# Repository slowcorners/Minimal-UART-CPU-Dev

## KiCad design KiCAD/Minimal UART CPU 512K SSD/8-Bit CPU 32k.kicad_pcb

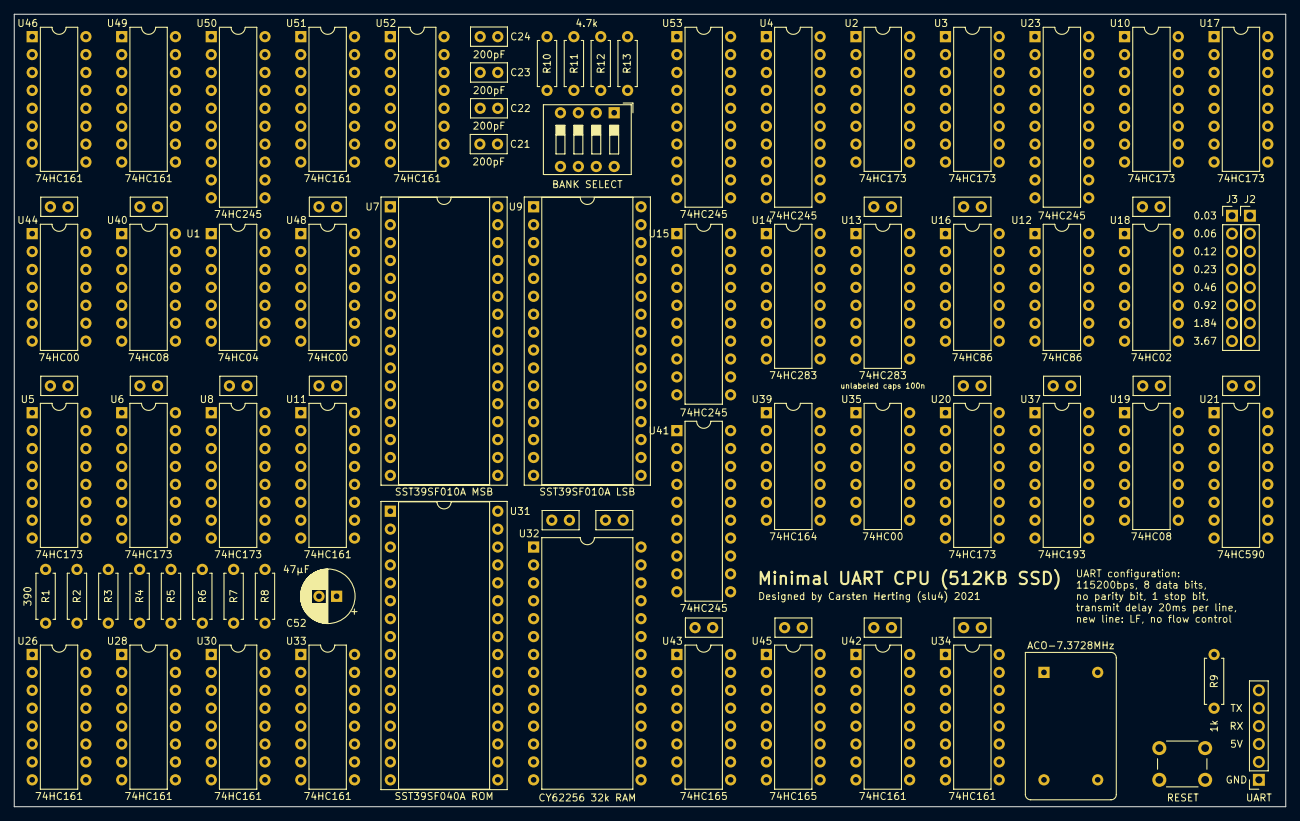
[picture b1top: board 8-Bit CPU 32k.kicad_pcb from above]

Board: 2 copper layers, 180.3 x 112.4 mm, 89 parts (0 on the bottom side), 170 nets, no tracks yet.

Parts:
C1, C2, C3, C4, C5, C6, C7, C8, C9, C10, C11, C12, C13, C14, C15, C16, C17, C18, C19, C20: 100nF; C_Disc_D5.0mm_W2.5mm_P2.50mm
C21, C22, C23, C24: 200pF; C_Disc_D5.0mm_W2.5mm_P2.50mm
C52: 47µF; CP_Radial_D7.5mm_P2.50mm
J1: UART; PinSocket_1x06_P2.54mm_Vertical
J2: CLOCK; PinHeader_1x08_P2.54mm_Vertical
J3: SELECT; PinHeader_1x08_P2.54mm_Vertical
R1, R2, R3, R4, R5, R6, R7, R8: 390; R_Axial_DIN0207_L6.3mm_D2.5mm_P7.62mm_Horizontal
R9: 1k; R_Axial_DIN0207_L6.3mm_D2.5mm_P7.62mm_Horizontal
R10, R11, R12, R13: 4.7k; R_Axial_DIN0207_L6.3mm_D2.5mm_P7.62mm_Horizontal
SW1: RESET; SW_PUSH_6mm
SW2: BANK SELECT; SW_DIP_SPSTx04_Slide_9.78x12.34mm_W7.62mm_P2.54mm
U1: 74HC04; DIP-14_W7.62mm
U2, U3, U5, U6, U8, U10, U17, U20: 74HC173; DIP-16_W7.62mm
U4, U15, U23, U41, U50, U53: 74HC245; DIP-20_W7.62mm
U7: SST39SF010A MSB; DIP-32_W15.24mm_Socket
U9: SST39SF010A LSB; DIP-32_W15.24mm_Socket
U11, U26, U28, U30, U33, U34, U42, U46, U49, U51, U52: 74HC161; DIP-16_W7.62mm
U12, U16: 74HC86; DIP-14_W7.62mm
U13, U14: 74HC283; DIP-16_W7.62mm
U18: 74HC02; DIP-14_W7.62mm
U19, U40: 74HC08; DIP-14_W7.62mm
U21: 74HC590; DIP-16_W7.62mm
U31: SST39SF040A ROM; DIP-32_W15.24mm_Socket
U32: CY62256 32k RAM; DIP-28_W15.24mm
U35, U44, U48: 74HC00; DIP-14_W7.62mm
U37: 74HC193; DIP-16_W7.62mm
U39: 74HC164; DIP-14_W7.62mm
U43, U45: 74HC165; DIP-16_W7.62mm
X1: ACO-7.3728MHz; Oscillator_DIP-14

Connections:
1.8432MHz: J3.2, U21.1, U34.2, U42.2
+5V: C1.1, C2.1, C3.1, C4.1, C5.1, C6.1, C7.1, C8.1, C9.1, C10.1, C11.1, C12.1, C13.1, C14.1, C15.1, C16.1, C17.1, C18.1, C19.1, C20.1, C52.1, J1.3, R1.1, R2.2, R3.2, R4.2, R5.2, R6.2, R7.2, R8.2, R9.2, SW2.5, SW2.6, SW2.7, SW2.8, U1.14, U2.16, U3.16, U4.1, U4.20, U5.16, U6.16, U7.31, U7.32, U8.16, U9.31, U9.32, U10.16, U11.7, U11.9, U11.10, U11.16, U12.14, U13.16, U14.16, U15.20, U16.14, U17.16, U18.14, U19.14, U20.16, U21.10, U21.16, U23.1, U23.20, U26.1, U26.16, U28.1, U28.16, U30.1, U30.16, U31.32, U32.28, U33.1, U33.16, U34.7, U34.9, U34.10, U34.16, U35.14, U37.5, U37.9, U37.15, U37.16, U39.2, U39.9, U39.14, U40.14, U41.1, U41.20, U42.7, U42.9, U42.10, U42.16, U43.6, U43.16, U44.14, U45.3, U45.4, U45.10, U45.11, U45.12, U45.13, U45.14, U45.16, U46.16, U48.14, U49.16, U50.20, U51.16, U52.16, U53.20, X1.14
/ALU/A0: U3.3, U4.2, U14.5
/ALU/A1: U3.4, U4.3, U14.3
/ALU/A2: U3.5, U4.4, U14.14
/ALU/A3: U3.6, U4.5, U14.12
/ALU/A4: U2.3, U4.6, U13.5
/ALU/A5: U2.4, U4.7, U13.3
/ALU/A6: U2.5, U4.8, U13.14
/ALU/A7: U2.6, U4.9, U13.12
/ALU/B0: U16.13, U17.3, U23.2
/ALU/B1: U16.10, U17.4, U23.3
/ALU/B2: U16.5, U17.5, U23.4
/ALU/B3: U16.2, U17.6, U23.5
/ALU/B4: U10.3, U12.13, U23.6
/ALU/B5: U10.4, U12.10, U23.7
/ALU/B6: U10.5, U12.5, U23.8
/ALU/B7: U10.6, U12.2, U23.9
/ALU/BUS0: R8.1, U3.14, U4.18, U8.14, U15.2, U17.14, U23.18, U28.3, U31.13, U32.11, U33.3, U41.11, U43.4, U49.3, U50.2, U52.3, U53.2
/ALU/BUS1: R7.1, U3.13, U4.17, U8.13, U15.3, U17.13, U23.17, U28.4, U31.14, U32.12, U33.4, U41.12, U43.3, U49.4, U50.3, U52.4, U53.3
/ALU/BUS2: R6.1, U3.12, U4.16, U8.12, U15.4, U17.12, U23.16, U28.5, U31.15, U32.13, U33.5, U41.13, U43.14, U49.5, U50.4, U52.5, U53.4
/ALU/BUS3: R5.1, U3.11, U4.15, U8.11, U15.5, U17.11, U23.15, U28.6, U31.17, U32.15, U33.6, U41.14, U43.13, U49.6, U50.5, U52.6, U53.5
/ALU/BUS4: R4.1, U2.14, U4.14, U6.14, U10.14, U15.6, U23.14, U26.3, U30.3, U31.18, U32.16, U41.15, U43.12, U46.3, U50.6, U51.3, U53.6
/ALU/BUS5: R3.1, U2.13, U4.13, U6.13, U10.13, U15.7, U23.13, U26.4, U30.4, U31.19, U32.17, U41.16, U43.11, U46.4, U50.7, U51.4, U53.7
/ALU/BUS6: R2.1, U2.12, U4.12, U10.12, U15.8, U23.12, U26.5, U30.5, U31.20, U32.18, U41.17, U45.6, U46.5, U50.8, U51.5, U53.8
/ALU/BUS7: R1.2, U2.11, U4.11, U10.11, U15.9, U23.11, U26.6, U30.6, U31.21, U32.19, U41.18, U45.5, U46.6, U50.9, U51.6, U53.9
/ALU/EC: U7.15, U14.7
/ALU/ES: U7.14, U12.1, U12.4, U12.9, U12.12, U16.1, U16.4, U16.9, U16.12
/ALU/FLAG_C: U5.13, U13.9
/ALU/FLAG_N: U5.12, U13.10, U15.11, U18.12
/ALU/FLAG_Z: U5.14, U19.6
/ALU/~EO: U5.9, U5.10, U7.13, U15.19
/Control Logic/CE: U1.3, U7.19, U26.7, U28.7, U30.7, U33.7, U33.10, U46.7, U49.7, U51.7, U52.7, U52.10
/Control Logic/CI: U7.21, U48.10, U48.12
/Control Logic/CO: U7.20, U48.2, U48.4
/Control Logic/HI: C23.2, U1.1, U9.21, U40.9, U44.5, U48.1, U48.13
/Control Logic/MI: U9.20, U44.2, U44.4
/Control Logic/RI: C24.2, U9.19, U44.9
/Control Logic/TI: U40.8, U44.12
/Control Logic/TO: U35.10, U40.3
/Control Logic/~AI: U2.9, U2.10, U3.9, U3.10, U9.17
/Control Logic/~AO: U4.19, U9.15
/Control Logic/~BI: U9.14, U10.9, U10.10, U17.9, U17.10
/Control Logic/~BO: U9.13, U23.19
/Control Logic/~HI: U1.2, U6.9, U8.9, U40.2, U44.1, U48.5, U48.9
/Control Logic/~RO: U9.18, U31.24, U32.22
/Memory/M0: U31.12, U32.21, U33.14
/Memory/M1: U31.11, U32.23, U33.13
/Memory/M2: U31.10, U32.24, U33.12
/Memory/M3: U31.9, U32.25, U33.11
/Memory/M4: U30.14, U31.8, U32.26
/Memory/M5: U30.13, U31.7, U32.1
/Memory/M6: U30.12, U31.6, U32.2
/Memory/M7: U30.11, U31.5, U32.3
/Memory/M8: U28.14, U31.27, U32.4
/Memory/M9: U28.13, U31.26, U32.5
/Memory/M10: U28.12, U31.23, U32.6
/Memory/M11: U28.11, U31.25, U32.7
/Memory/M12: U26.14, U31.4, U32.8
/Memory/M13: U26.13, U31.28, U32.9
/Memory/M14: U26.12, U31.29, U32.10
/Memory/M15: U1.9, U26.11, U31.22
/UART Receiver/RX: J1.4, U35.1, U39.1
/UART Transmitter/TX: J1.5, U43.9
CLOCK: J2.1, J2.2, J2.3, J2.4, J2.5, J2.6, J2.7, J2.8, U1.13, U2.7, U3.7, U5.7, U6.7, U8.7, U10.7, U17.7, U26.2, U28.2, U30.2, U33.2, U35.13, U44.10, U44.13, U46.2, U49.2, U51.2, U52.2
GND: C1.2, C2.2, C3.2, C4.2, C5.2, C6.2, C7.2, C8.2, C9.2, C10.2, C11.2, C12.2, C13.2, C14.2, C15.2, C16.2, C17.2, C18.2, C19.2, C20.2, C21.1, C22.1, C23.1, C24.1, C52.2, J1.1, R10.2, R11.2, R12.2, R13.2, SW1.1, U1.7, U2.1, U2.2, U2.8, U2.15, U3.1, U3.2, U3.8, U3.15, U4.10, U5.1, U5.2, U5.8, U5.11, U5.15, U6.1, U6.2, U6.8, U6.11, U6.12, U6.15, U7.2, U7.3, U7.16, U7.22, U7.24, U7.28, U7.29, U8.1, U8.2, U8.8, U8.15, U9.2, U9.3, U9.16, U9.22, U9.24, U9.28, U9.29, U10.1, U10.2, U10.8, U10.15, U11.8, U12.7, U13.8, U14.8, U15.1, U15.10, U16.7, U17.1, U17.2, U17.8, U17.15, U18.7, U19.7, U20.1, U20.2, U20.8, U20.9, U20.10, U20.11, U20.12, U20.13, U20.15, U21.8, U21.12, U21.14, U23.10, U26.8, U28.8, U30.8, U31.16, U32.14, U33.8, U34.8, U35.7, U37.1, U37.8, U37.10, U37.14, U39.7, U40.7, U40.12, U40.13, U41.10, U42.8, U43.5, U43.8, U43.15, U44.7, U45.8, U45.15, U46.8, U48.7, U49.8, U50.1, U50.10, U51.8, U52.8, U53.1, U53.10, X1.7
unnamed: C21.2, U7.18, U40.1, U40.10
unnamed: C22.2, U7.17, U40.5
unnamed: J3.1, U21.15
unnamed: J3.3, U21.2
unnamed: J3.4, U21.3
unnamed: J3.5, U21.4
unnamed: J3.6, U21.5
unnamed: J3.7, U21.6
unnamed: J3.8, U21.7
unnamed: R10.1, SW2.4, U31.1
unnamed: R11.1, SW2.3, U31.30
unnamed: R12.1, SW2.2, U31.2
unnamed: R13.1, SW2.1, U31.3
unnamed: U1.4, U6.10, U8.10
unnamed: U1.5, U19.10, U37.13
unnamed: U1.6, U20.14
unnamed: U1.8, U32.20
unnamed: U1.10, U35.12
unnamed: U1.11, U35.8, U41.19
unnamed: U5.3, U7.23, U9.23
unnamed: U5.4, U7.25, U9.25
unnamed: U5.5, U7.4, U9.4
unnamed: U6.3, U7.27, U9.27
unnamed: U6.4, U7.26, U9.26
unnamed: U7.5, U8.6, U9.5
unnamed: U7.6, U8.5, U9.6
unnamed: U7.7, U8.4, U9.7
unnamed: U7.8, U8.3, U9.8
unnamed: U11.1, U40.6
unnamed: U7.9, U9.9, U11.11
unnamed: U7.10, U9.10, U11.12
unnamed: U7.11, U9.11, U11.13
unnamed: U7.12, U9.12, U11.14
unnamed: U12.3, U13.11
unnamed: U12.6, U13.15
unnamed: U12.8, U13.2
unnamed: U12.11, U13.6
unnamed: U13.1, U15.13, U18.9
unnamed: U13.4, U15.14, U18.8
unnamed: U13.7, U14.9
unnamed: U13.13, U15.12, U18.11
unnamed: U14.1, U15.17, U18.3
unnamed: U14.2, U16.8
unnamed: U14.4, U15.18, U18.2
unnamed: U14.6, U16.11
unnamed: U14.10, U15.15, U18.6
unnamed: U14.11, U16.3
unnamed: U14.13, U15.16, U18.5
unnamed: U14.15, U16.6
unnamed: U18.1, U19.1
unnamed: U18.4, U19.2
unnamed: U18.10, U19.12
unnamed: U18.13, U19.13
unnamed: U19.3, U19.4
unnamed: U19.8, U34.1
unnamed: U19.9, U35.3, U35.4, U37.11
unnamed: U19.5, U19.11
unnamed: U20.3, U35.9
unnamed: U21.11, U21.13, X1.8
unnamed: U26.9, U28.9, U44.6
unnamed: U26.10, U28.15
unnamed: U28.10, U30.15
unnamed: U30.9, U33.9, U44.3
unnamed: U30.10, U33.15
unnamed: U31.31, U32.27, U44.8
unnamed: U34.11, U37.4, U39.8
unnamed: U35.2, U35.6
unnamed: U35.5, U35.11
unnamed: U39.3, U41.2
unnamed: U39.4, U41.3
unnamed: U39.5, U41.4
unnamed: U39.6, U41.5
unnamed: U39.10, U41.6
unnamed: U39.11, U41.7
unnamed: U39.12, U41.8
unnamed: U39.13, U41.9
unnamed: U42.1, U43.1, U44.11, U45.1
unnamed: U42.11, U43.2, U45.2
unnamed: U43.10, U45.9
unnamed: U46.9, U48.11, U49.9
unnamed: U46.10, U49.15
unnamed: U46.11, U50.11
unnamed: U46.12, U50.12
unnamed: U46.13, U50.13
unnamed: U46.14, U50.14
unnamed: U48.3, U50.19
unnamed: U48.6, U53.19
unnamed: U48.8, U51.9, U52.9
unnamed: U49.10, U51.15
unnamed: U49.11, U50.15
unnamed: U49.12, U50.16
unnamed: U49.13, U50.17
unnamed: U49.14, U50.18
unnamed: U51.10, U52.15
unnamed: U51.11, U53.11
unnamed: U51.12, U53.12
unnamed: U51.13, U53.13
unnamed: U51.14, U53.14
unnamed: U52.11, U53.15
unnamed: U52.12, U53.16
unnamed: U52.13, U53.17
unnamed: U52.14, U53.18
~CLOCK: U1.12, U11.2, U20.7
~RESET: R9.1, SW1.2, U40.4, U46.1, U49.1, U51.1, U52.1

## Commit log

2021-03-09 Now the emulator is up to speed
    Implemented breakpoints, cycle-exact UART and FLASH behavior.
    So now the load, save, format, erase function are working as expected.
    Cheers,
    slu4
